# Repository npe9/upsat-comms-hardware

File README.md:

# UPSat communications hardware

Hardware for UPSat communications subsystem and for the antenna deployment mechanism. This repository includes all needed.

## Documentation

## Repository policy
UPSat hardware repositories only track source design files. All needed derivative files (e.g. stl, grb etc) for production are created per release, packaged in an archive and uploaded linked to a  [release](*link needed*).

Each major release (x.0.0) is branched out of master. Subsequent fixes (minor or not) are commited on those branches and tagged accordingly.

Master branch is most times under active development, so expect things to break. For production ready and previous releases source files check tags and branches.

## License

&copy; 2016 Manos Theodoridis - APEL - University of Patras
&copy; 2016 Libre Space Foundation & commiters

Licensed under the [CERN OHLv1.2](LICENSE).

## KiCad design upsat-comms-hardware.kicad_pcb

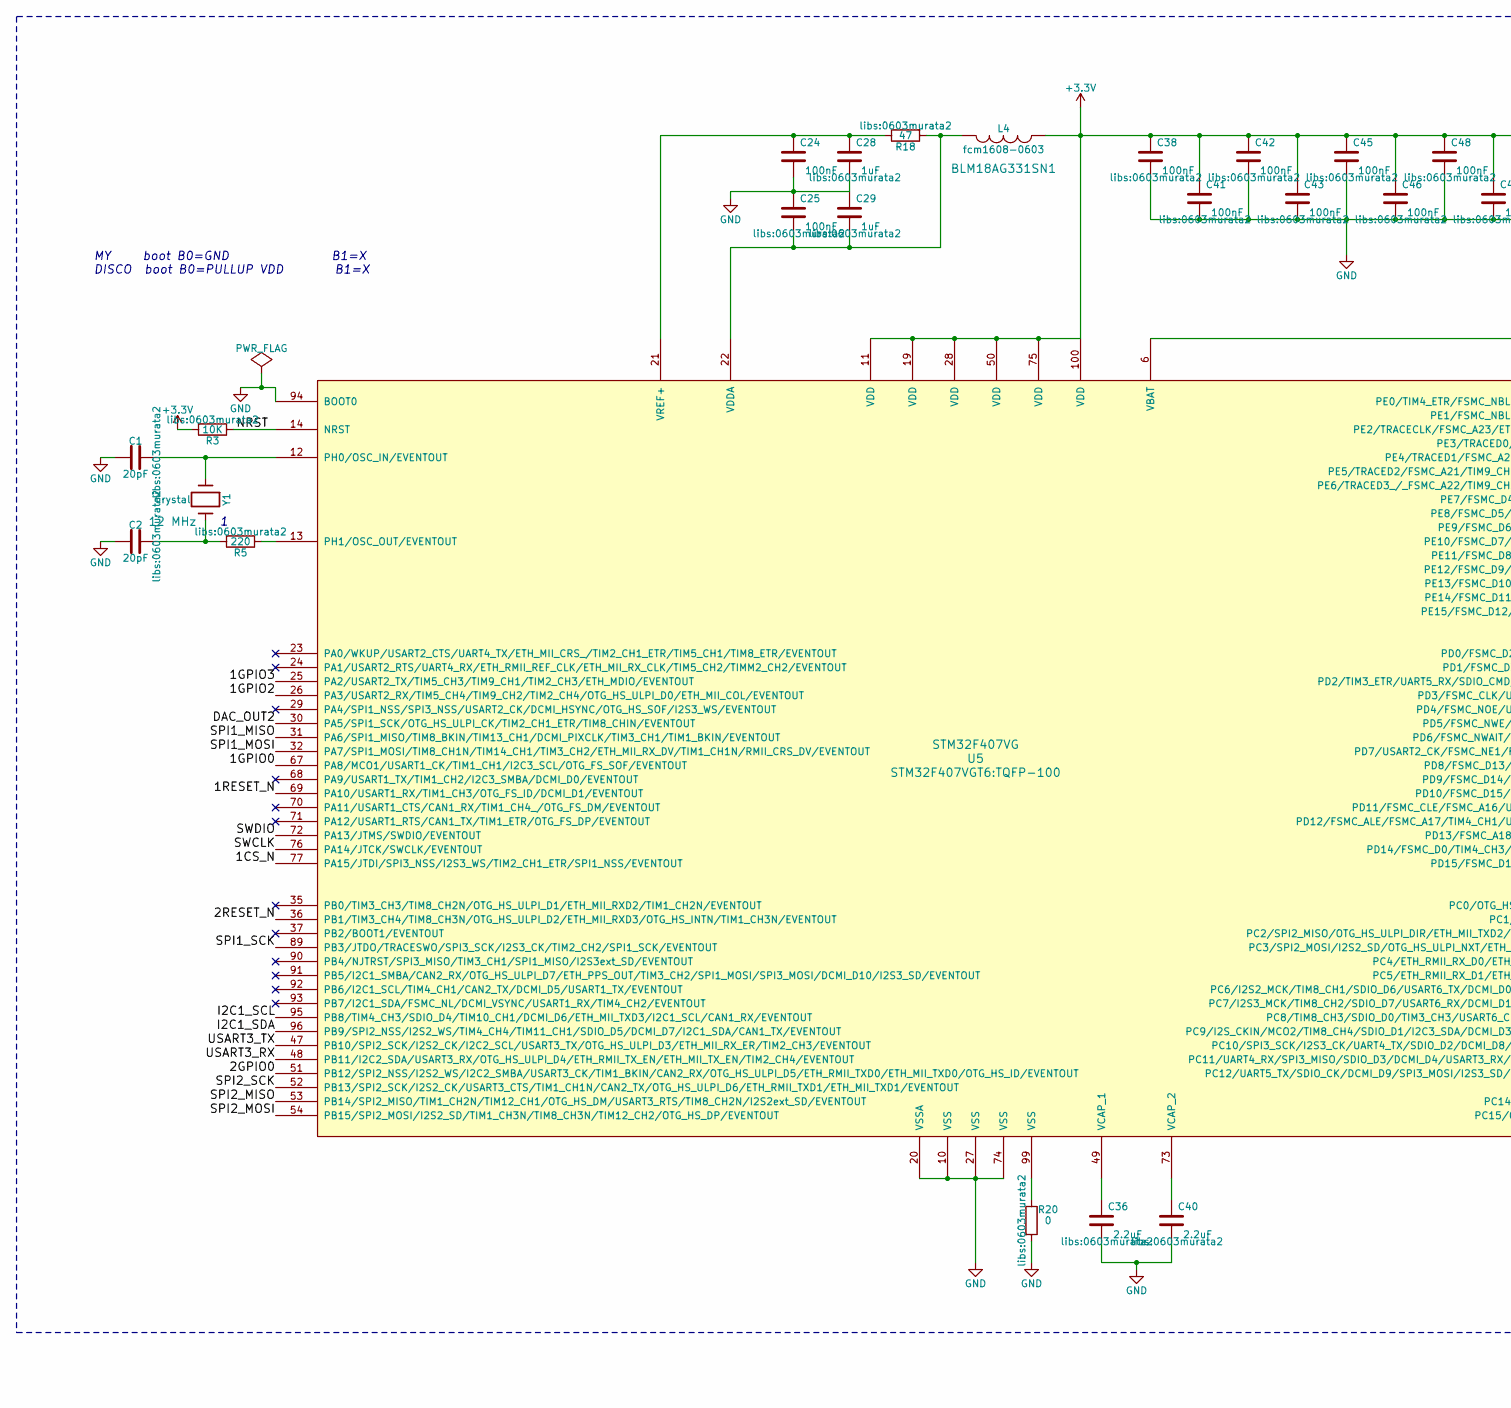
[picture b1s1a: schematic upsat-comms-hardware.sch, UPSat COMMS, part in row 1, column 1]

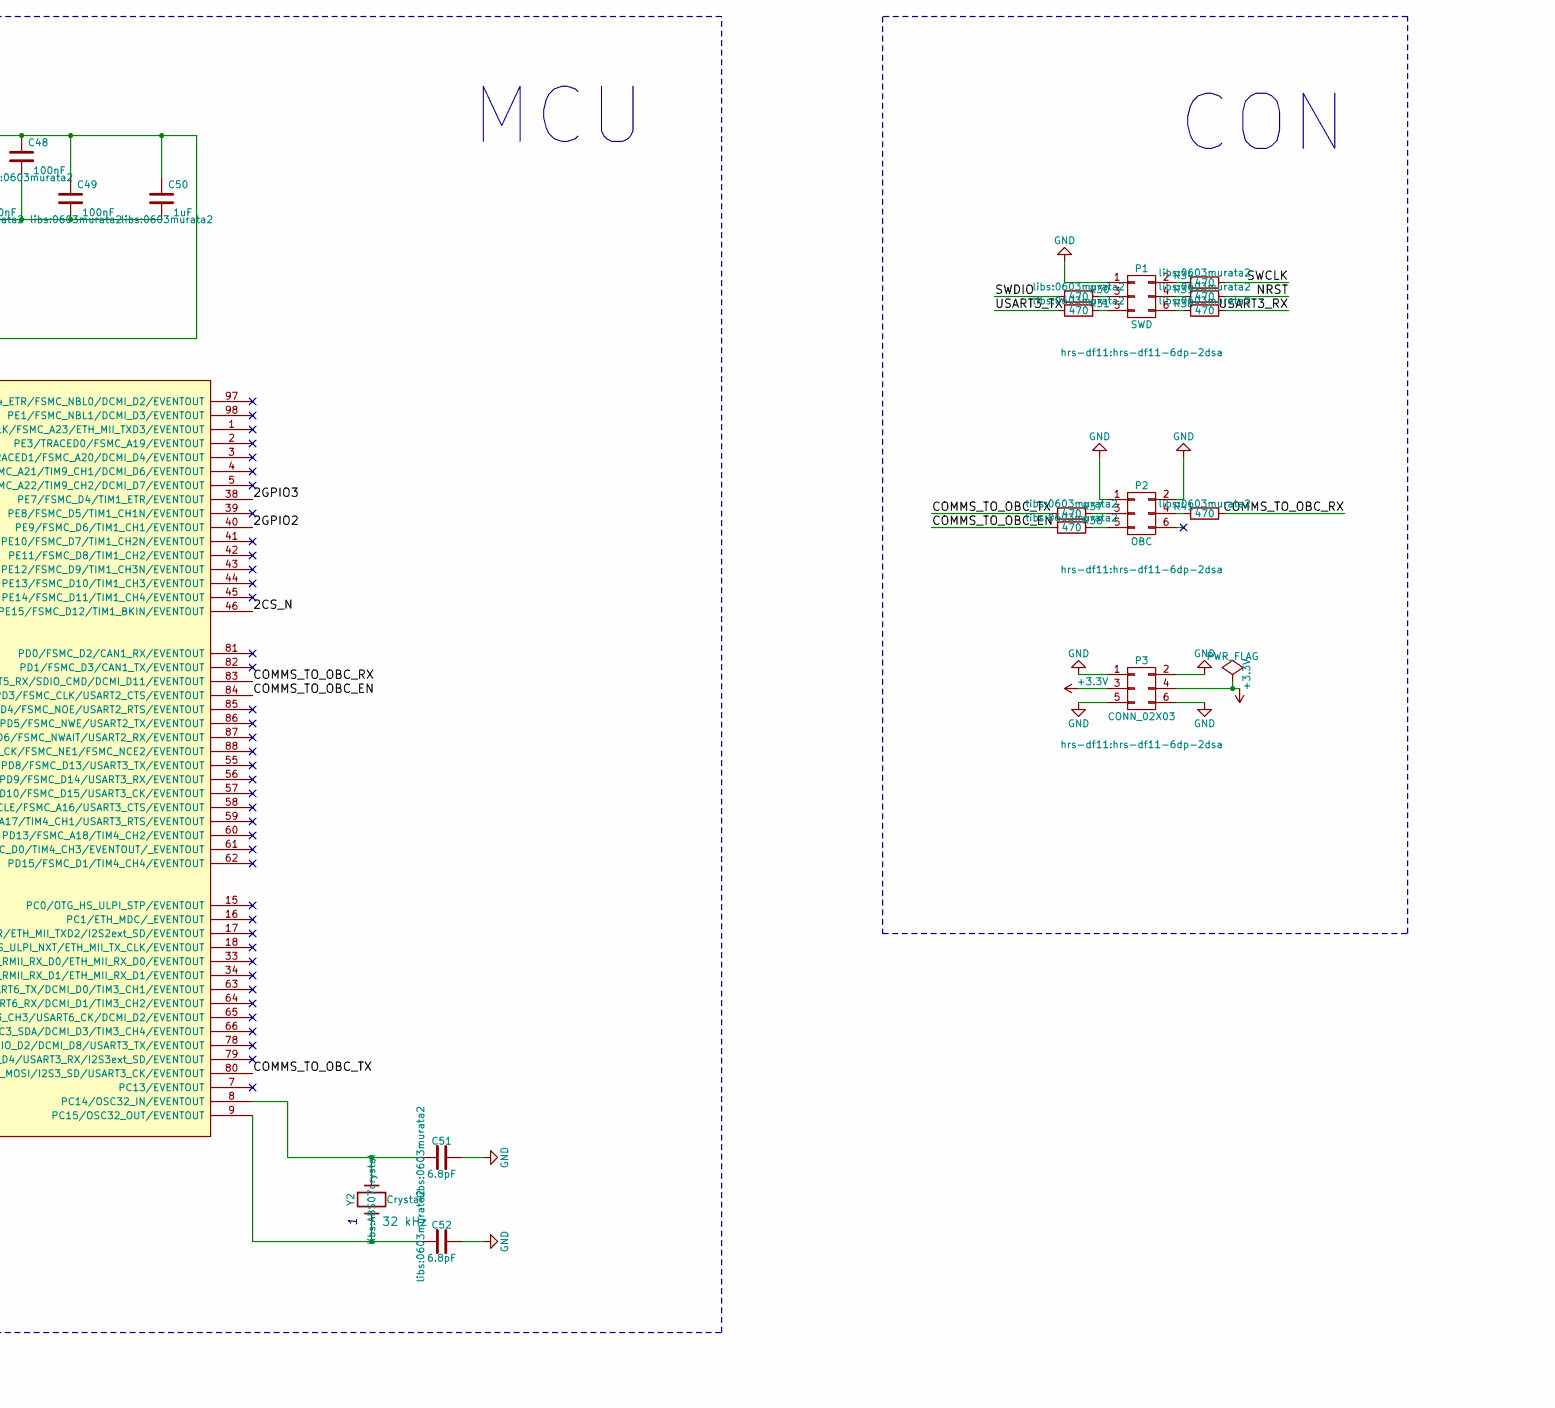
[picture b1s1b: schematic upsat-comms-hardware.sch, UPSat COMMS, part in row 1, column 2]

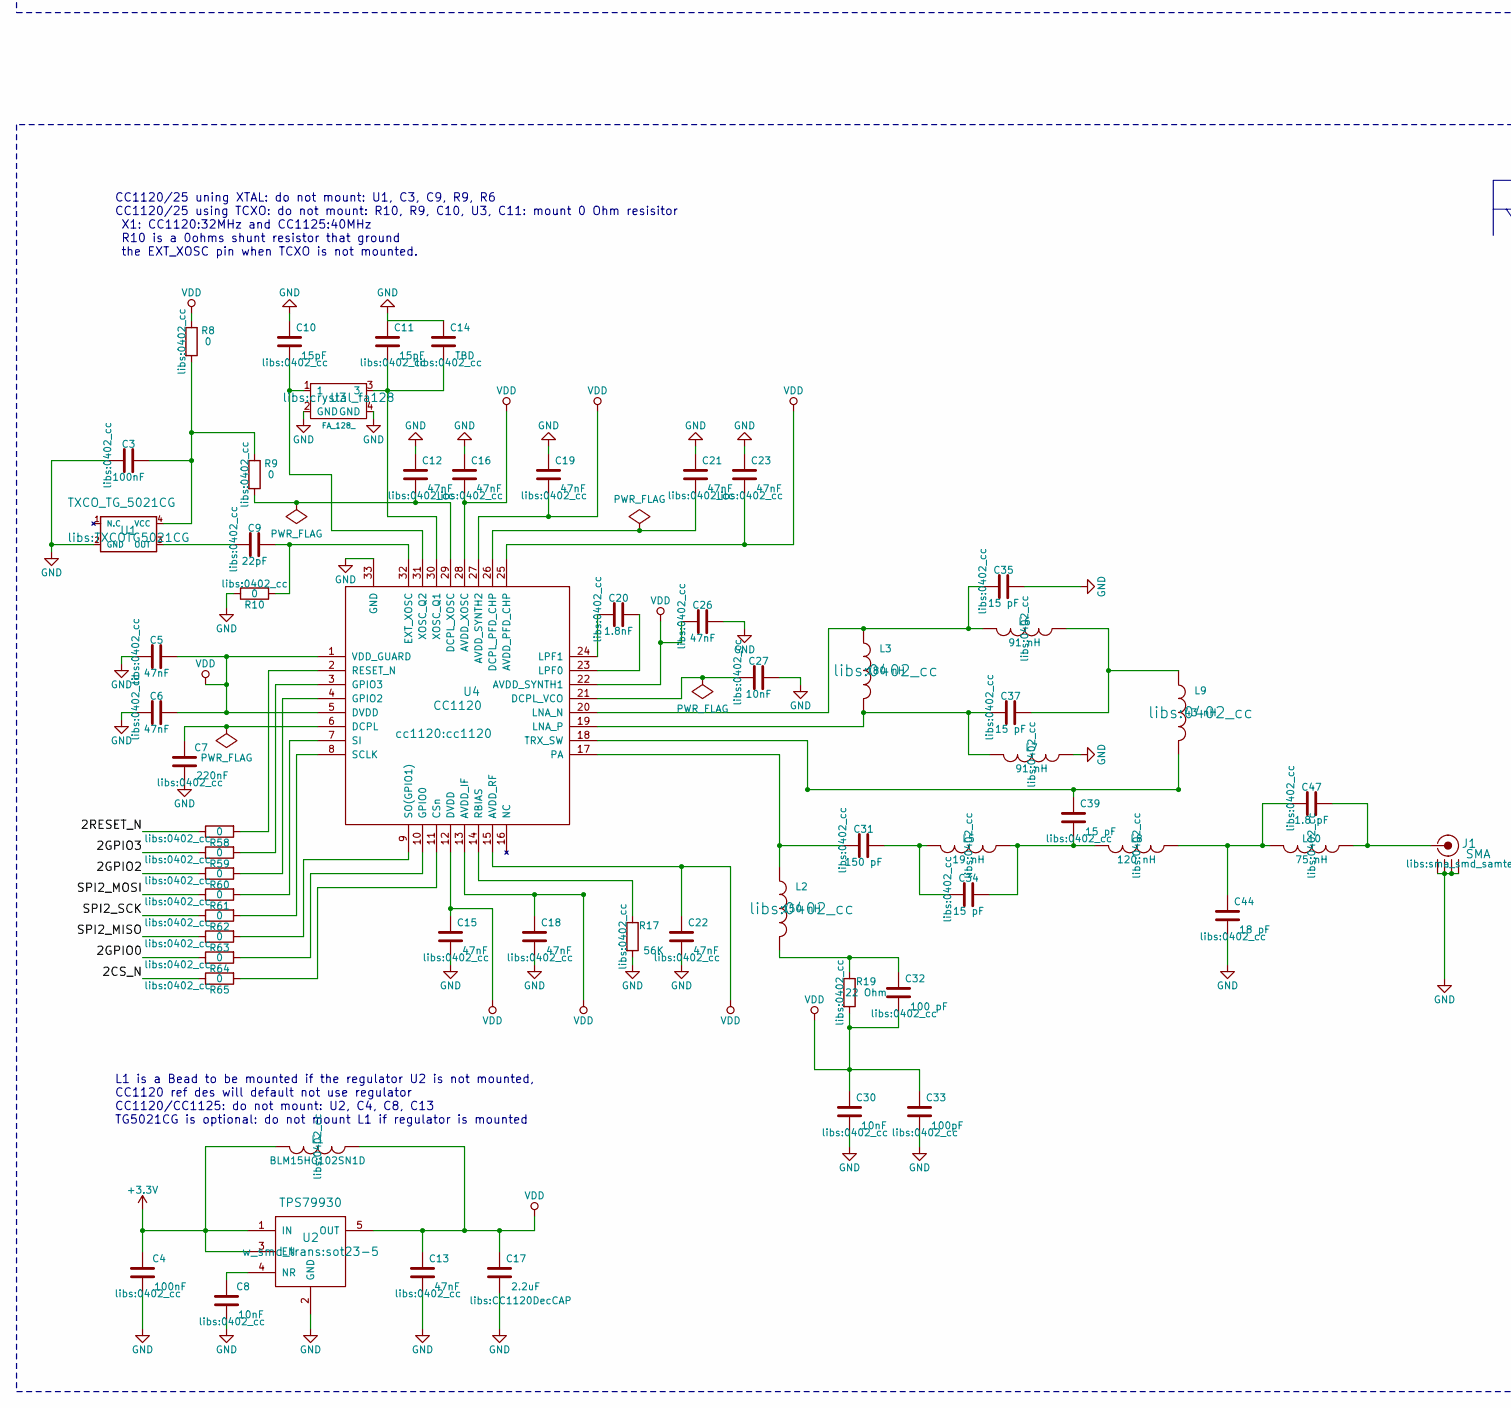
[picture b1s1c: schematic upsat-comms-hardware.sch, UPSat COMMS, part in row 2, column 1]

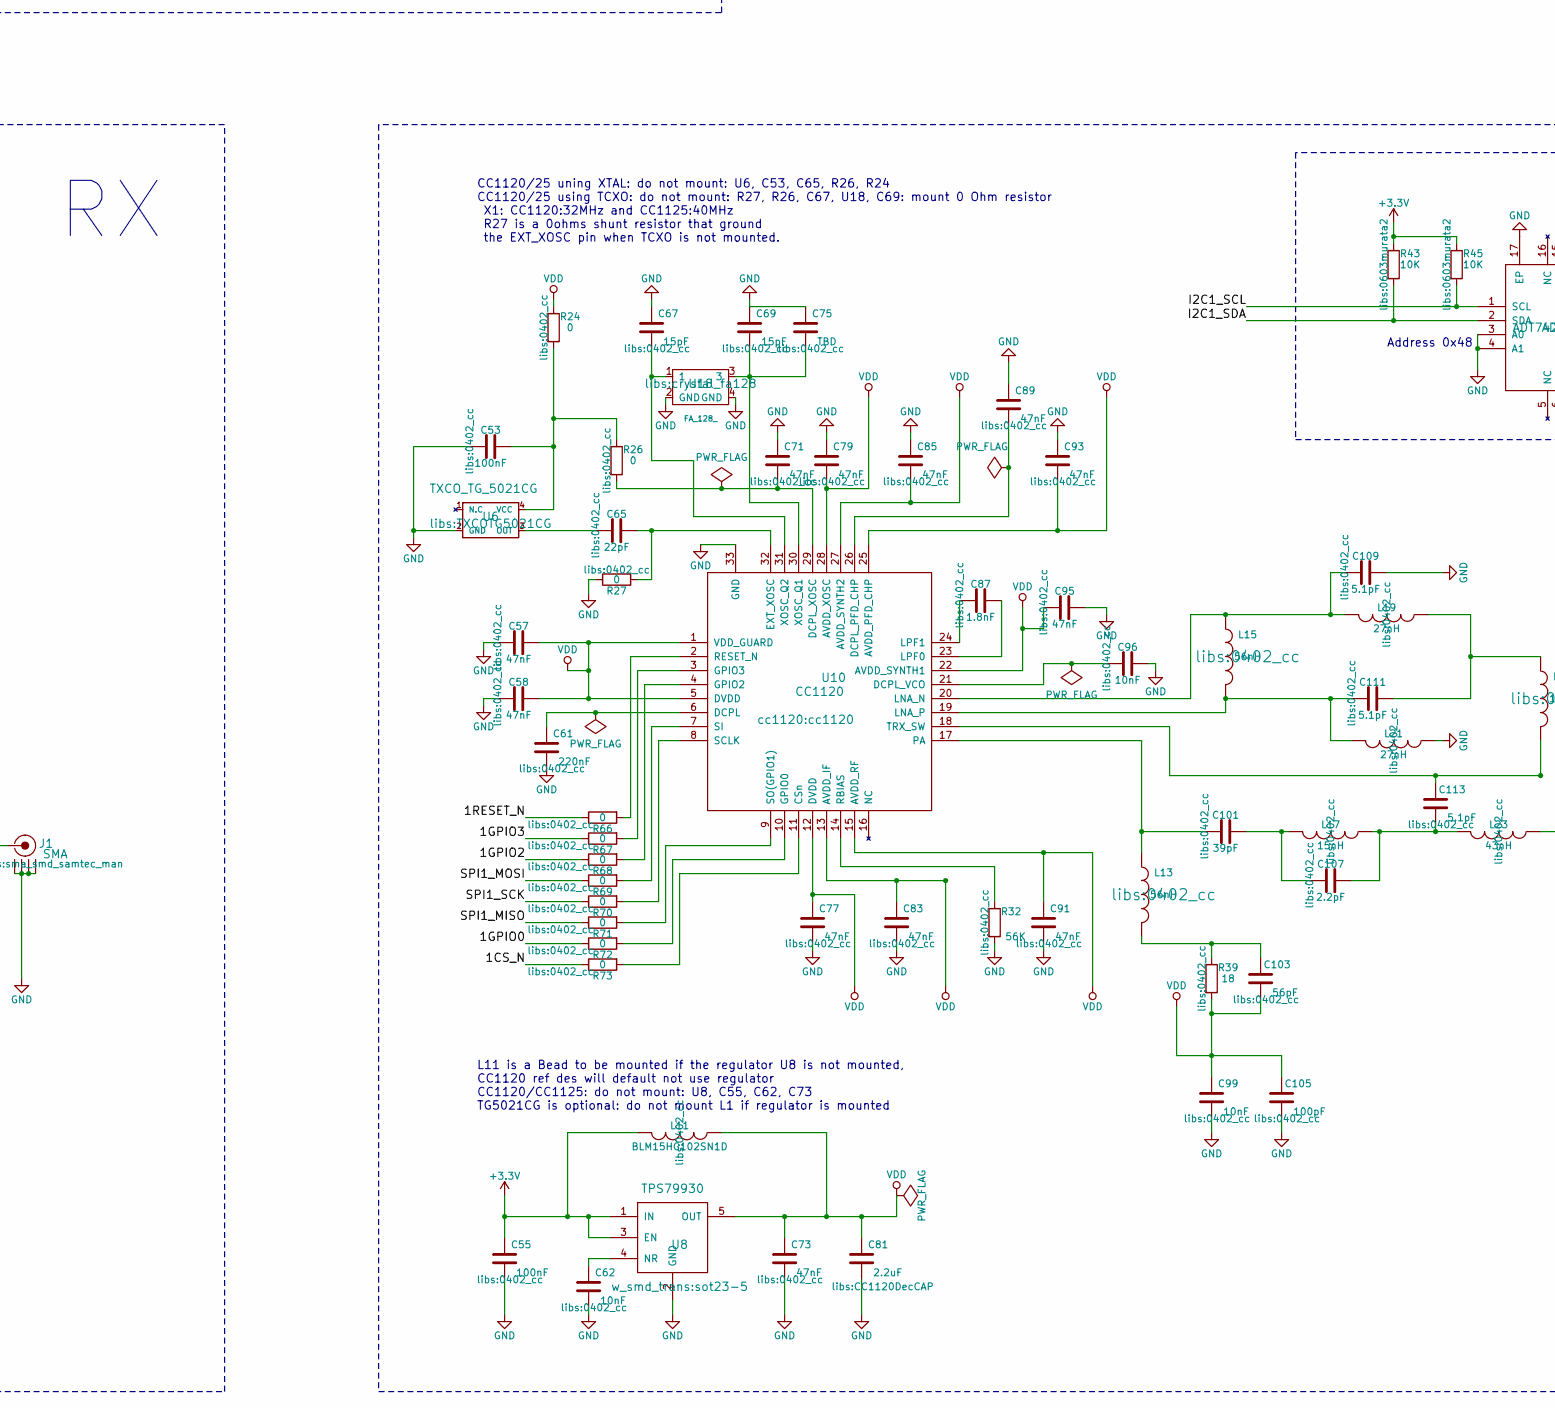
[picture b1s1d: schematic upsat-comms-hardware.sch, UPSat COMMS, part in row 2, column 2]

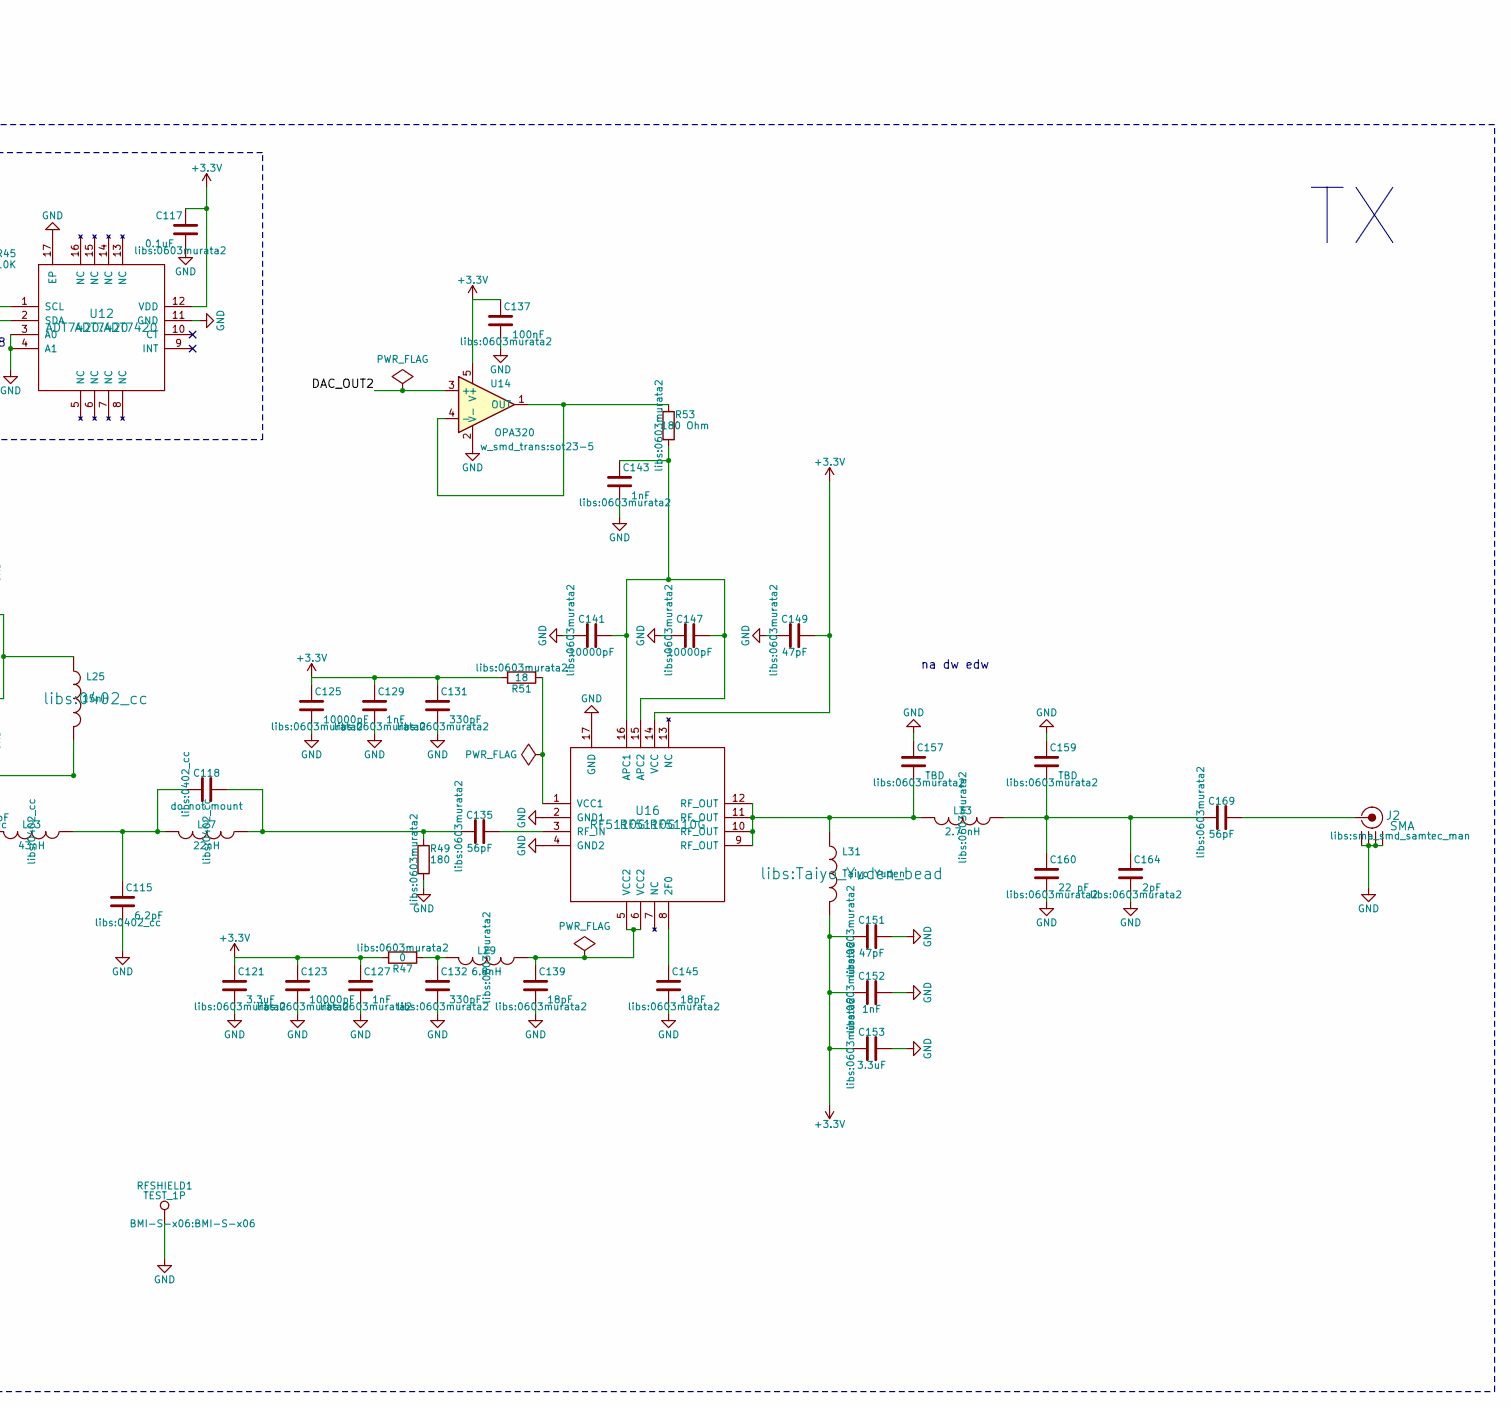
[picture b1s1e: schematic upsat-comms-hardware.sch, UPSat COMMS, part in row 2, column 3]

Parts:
C1, C2: 20pF; 0603murata2
C3, C4, C53, C55: 100nF; 0402_cc
C5, C6, C12, C13, C15, C16, C18, C19, C21, C22, C23, C26, C57, C58, C71, C73, C77, C79, C83, C85, C89, C91, C93, C95: 47nF; 0402_cc
C7, C61: 220nF; 0402_cc
C8, C27, C30, C62, C96, C99: 10nF; 0402_cc
C9, C65: 22pF; 0402_cc
C10, C11, C67, C69: 15pF; 0402_cc
C14, C75: TBD; 0402_cc
C17, C81: 2.2uF; CC1120DecCAP
C20, C87: 1.8nF; 0402_cc
C24, C25, C38, C41, C42, C43, C45, C46, C48, C49, C137: 100nF; 0603murata2
C28, C29, C50: 1uF; 0603murata2
C31: 150 pF; 0402_cc
C32: 100 pF; 0402_cc
C33, C105: 100pF; 0402_cc
C34, C35, C37, C39: 15 pF; 0402_cc
C36, C40: 2.2uF; 0603murata2
C44: 18 pF; 0402_cc
C47: 1.8 pF; 0402_cc
C51, C52: 6.8pF; 0603murata2
C101: 39pF; 0402_cc
C103: 56pF; 0402_cc
C107: 2.2pF; 0402_cc
C109, C111, C113: 5.1pF; 0402_cc
C115: 6.2pF; 0402_cc
C117: 0.1uF; 0603murata2
C118: do not mount; 0402_cc
C121, C153: 3.3uF; 0603murata2
C123, C125, C141, C147: 10000pF; 0603murata2
C127, C129, C143, C152: 1nF; 0603murata2
C131, C132: 330pF; 0603murata2
C135, C169: 56pF; 0603murata2
C139, C145: 18pF; 0603murata2
C149, C151: 47pF; 0603murata2
C157, C159: TBD; 0603murata2
C160: 22 pF; 0603murata2
C164: 2pF; 0603murata2
J1, J2: SMA; sma_smd_samtec_man
L1, L11: BLM15HG102SN1D; 0402_cc
L2: 150 nH; 0402_cc
L3: 180 nH; 0402_cc
L4: fcm1608-0603; 0603murata2
L5: 19 nH; 0402_cc
L6, L7: 91 nH; 0402_cc
L8: 120 nH; 0402_cc
L9: 43 nH; 0402_cc
L10: 75 nH; 0402_cc
L13, L15: 56nH; 0402_cc
L17, L25: 15nH; 0402_cc
L19, L21: 27nH; 0402_cc
L23: 43nH; 0402_cc
L27: 22nH; 0402_cc
L29: 6.8nH; 0603murata2
L31: Taiyo Yuden; Taiyo_Yuden_bead
L33: 2.7 nH; 0603murata2
P1: SWD; hrs-df11-6dp-2dsa
P2: OBC; hrs-df11-6dp-2dsa
P3: CONN_02X03; hrs-df11-6dp-2dsa
R3, R43, R45: 10K; 0603murata2
R5: 220; 0603murata2
R8, R9, R10, R24, R26, R27, R58, R59, R60, R61, R62, R63, R64, R65, R66, R67, R68, R69, R70, R71, R72, R73: 0; 0402_cc
R17, R32: 56K; 0402_cc
R18: 47; 0603murata2
R19: 22 Ohm; 0402_cc
R20, R47: 0; 0603murata2
R30, R31, R34, R35, R36, R37, R38, R41: 470; 0603murata2
R39: 18; 0402_cc
R49: 180; 0603murata2
R51: 18; 0603murata2
R53: 180 Ohm; 0603murata2
RFSHIELD1: TEST_1P; BMI-S-x06
U1, U6: TXCO_TG_5021CG; TXCOTG5021CG
U2, U8: TPS79930; sot23-5
U3, U18: FA_128_; crystal_fa128
U4, U10: CC1120; cc1120
U5: STM32F407VG; TQFP-100
U12: ADT7420
U14: OPA320; sot23-5
U16: RF5110G
Y1: Crystal; ABM3crystal
Y2: Crystal; ABS07crystal

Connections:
+3V3: C4.1, C38.1, C41.1, C42.1, C43.1, C45.1, C46.1, C48.1, C49.1, C50.1, C55.1, C117.1, C121.1, C123.1, C125.1, C127.1, C129.1, C131.1, C137.1, C149.1, C151.2, C152.2, C153.2, L1.2, L4.2, L11.2, L31.2, P3.3, P3.4, R3.2, R43.1, R45.1, R47.1, R51.1, U2.1 (IN), U2.3 (EN), U5.6 (VBAT), U5.11 (VDD), U5.19 (VDD), U5.28 (VDD), U5.50 (VDD), U5.75 (VDD), U5.100 (VDD), U8.1 (IN), U8.3 (EN), U12.12 (VDD), U14.5 (V+), U16.14 (VCC); also elsewhere on the board
/1CS_N: R73.1, U5.77 (PA15/JTDI/SPI3_NSS/I2S3_WS/TIM2_CH1_ETR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)
/1GPIO0: R72.1, U5.67 (PA8/MCO1/USART1_CK/TIM1_CH1/I2C3_SCL/OT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)
/1GPIO2: R68.1, U5.26 (PA3/USART2_RX/TIM5_CH4/TIM9_CH2/TIM2_CH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)
/1GPIO3: R67.1, U5.25 (PA2/USART2_TX/TIM5_CH3/TIM9_CH1/TIM2_CH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)
/1RESET_N: R66.1, U5.69 (PA10/USART1_RX/TIM1_CH3/OTG_FS_ID/DCMI_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)
/2CS_N: R65.1, U5.46 (PE15/FSMC_D12/TIM1_BKIN/EVENTOUT)
/2GPIO0: R64.1, U5.51 (PB12/SPI2_NSS/I2S2_WS/I2C2_SMBA/USART3_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)
/2GPIO2: R60.1, U5.40 (PE9/FSMC_D6/TIM1_CH1/EVENTOUT)
/2GPIO3: R59.1, U5.38 (PE7/FSMC_D4/TIM1_ETR/EVENTOUT)
/2RESET_N: R58.1, U5.36 (PB1/TIM3_CH4/TIM8_CH3N/OTG_HS_ULPI_D2/E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)
/COMMS_TO_OBC_EN: R38.2, U5.84 (PD3/FSMC_CLK/USART2_CTS/EVENTOUT)
/COMMS_TO_OBC_RX: R41.1, U5.83 (PD2/TIM3_ETR/UART5_RX/SDIO_CMD/DCMI_D11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)
/COMMS_TO_OBC_TX: R37.2, U5.80 (PC12/UART5_TX/SDIO_CK/DCMI_D9/SPI3_MOSI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)
/DAC_OUT2: U5.30 (PA5/SPI1_SCK/OTG_HS_ULPI_CK/TIM2_CH1_ET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), U14.3 (+)
/I2C1_SCL: R45.2, U5.95 (PB8/TIM4_CH3/SDIO_D4/TIM10_CH1/DCMI_D6/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), U12.1 (SCL)
/I2C1_SDA: R43.2, U5.96 (PB9/SPI2_NSS/I2S2_WS/TIM4_CH4/TIM11_CH1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), U12.2 (SDA)
/NRST: R3.1, R35.1, U5.14 (NRST)
/SPI1_MISO: R71.1, U5.31 (PA6/SPI1_MISO/TIM8_BKIN/TIM13_CH1/DCMI_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)
/SPI1_MOSI: R69.1, U5.32 (PA7/SPI1_MOSI/TIM8_CH1N/TIM14_CH1/TIM3_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)
/SPI1_SCK: R70.1, U5.89 (PB3/JTDO/TRACESWO/SPI3_SCK/I2S3_CK/TIM2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)
/SPI2_MISO: R63.1, U5.53 (PB14/SPI2_MISO/TIM1_CH2N/TIM12_CH1/OTG_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)
/SPI2_MOSI: R61.1, U5.54 (PB15/SPI2_MOSI/I2S2_SD/TIM1_CH3N/TIM8_C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)
/SPI2_SCK: R62.1, U5.52 (PB13/SPI2_SCK/I2S2_CK/USART3_CTS/TIM1_C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)
/SWCLK: R34.1, U5.76 (PA14/JTCK/SWCLK/EVENTOUT)
/SWDIO: R30.2, U5.72 (PA13/JTMS/SWDIO/EVENTOUT)
/USART3_RX: R36.1, U5.48 (PB11/I2C2_SDA/USART3_RX/OTG_HS_ULPI_D4/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)
/USART3_TX: R31.2, U5.47 (PB10/SPI2_SCK/I2S2_CK/I2C2_SCL/USART3_T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)
GND: C1.1, C2.1, C3.2, C4.2, C5.2, C6.2, C7.2, C8.2, C10.1, C11.1, C12.1, C13.2, C14.1, C15.2, C16.1, C17.2, C18.2, C19.1, C21.1, C22.2, C23.1, C24.2, C25.1, C26.1, C27.1, C28.2, C29.1, C30.2, C33.2, C35.1, C36.2, C38.2, C40.2, C41.2, C42.2, C43.2, C44.2, C45.2, C46.2, C48.2, C49.2, C50.2, C51.1, C52.1, C53.2, C55.2, C57.2, C58.2, C61.2, C62.2, C67.1, C69.1, C71.1, C73.2, C75.1, C77.2, C79.1, C81.2, C83.2, C85.1, C89.1, C91.2, C93.1, C95.1, C96.1, C99.2, C105.2, C109.1, C115.2, C117.2, C121.2, C123.2, C125.2, C127.2, C129.2, C131.2, C132.2, C137.2, C139.2, C141.2, C143.2, C145.2, C147.2, C149.2, C151.1, C152.1, C153.1, C157.1, C159.1, C160.2, C164.2, J1.2 (GND1), J1.3 (GND2), J1.4 (GND3), J1.5 (GND4), J2.2 (GND1), J2.3 (GND2), J2.4 (GND3), J2.5 (GND4), L7.1, L21.1, P1.1, P2.1, P2.2, P3.1, P3.2, P3.5, P3.6, R10.1, R17.2, R20.2, R27.1, R32.2, R49.2, RFSHIELD1.1, U1.2 (GND), U2.2 (GND), U3.2 (GND), U3.4 (GND), U4.33 (GND), U5.10 (VSS), U5.20 (VSSA), U5.27 (VSS), U5.74 (VSS), U5.94 (BOOT0), U6.2 (GND), U8.2 (GND), U10.33 (GND), U12.3 (A0), U12.4 (A1), U12.11 (GND), U12.17 (EP), U14.2 (V-), U16.2 (GND1), U16.4 (GND2), U16.17 (GND), U18.2 (GND), U18.4 (GND); also elsewhere on the board
unnamed: C1.2, U5.12 (PH0/OSC_IN/EVENTOUT), Y1.1
unnamed: C2.2, R5.2, Y1.2
unnamed: C3.1, R8.2, R9.1, U1.4 (VCC)
unnamed: C7.1, U4.6 (DCPL)
unnamed: C8.1, U2.4 (NR)
unnamed: C9.1, R10.2, U4.32 (EXT_XOSC)
unnamed: C9.2, U1.3 (OUT)
unnamed: C10.2, U3.1, U4.31 (XOSC_Q2)
unnamed: C11.2, C14.2, U3.3, U4.30 (XOSC_Q1)
unnamed: C12.2, R9.2, U4.29 (DCPL_XOSC)
unnamed: C20.1, U4.23 (LPF0)
unnamed: C20.2, U4.24 (LPF1)
unnamed: C21.2, U4.26 (DCPL_PFD_CHP)
unnamed: C24.1, C28.1, R18.1, U5.21 (VREF+)
unnamed: C25.2, C29.2, L4.1, R18.2, U5.22 (VDDA)
unnamed: C27.2, U4.21 (DCPL_VCO)
unnamed: C31.1, C34.2, L5.2
unnamed: C31.2, L2.1, U4.17 (PA)
unnamed: C32.1, L2.2, R19.1
unnamed: C34.1, C39.2, L5.1, L8.2
unnamed: C35.2, L3.1, L6.2, U4.20 (LNA_N)
unnamed: C36.1, U5.49 (VCAP_1)
unnamed: C37.1, L6.1, L9.1
unnamed: C37.2, L3.2, L7.2, U4.19 (LNA_P)
unnamed: C39.1, L9.2, U4.18 (TRX_SW)
unnamed: C40.1, U5.73 (VCAP_2)
unnamed: C44.1, C47.2, L8.1, L10.2
unnamed 56: C47.1, J1.1 (RF), L10.1; also elsewhere on the board
unnamed: C51.2, U5.8 (PC14/OSC32_IN/EVENTOUT), Y2.1
unnamed: C52.2, U5.9 (PC15/OSC32_OUT/EVENTOUT), Y2.2
unnamed: C53.1, R24.2, R26.1, U6.4 (VCC)
unnamed: C61.1, U10.6 (DCPL)
unnamed: C62.1, U8.4 (NR)
unnamed: C65.1, R27.2, U10.32 (EXT_XOSC)
unnamed: C65.2, U6.3 (OUT)
unnamed: C67.2, U10.31 (XOSC_Q2), U18.1
unnamed: C69.2, C75.2, U10.30 (XOSC_Q1), U18.3
unnamed: C71.2, R26.2, U10.29 (DCPL_XOSC)
unnamed: C87.1, U10.23 (LPF0)
unnamed: C87.2, U10.24 (LPF1)
unnamed: C89.2, U10.26 (DCPL_PFD_CHP)
unnamed: C96.2, U10.21 (DCPL_VCO)
unnamed: C101.1, C107.2, L17.2
unnamed: C101.2, L13.1, U10.17 (PA)
unnamed: C103.1, L13.2, R39.1
unnamed: C107.1, C113.2, L17.1, L23.2
unnamed: C109.2, L15.1, L19.2, U10.20 (LNA_N)
unnamed: C111.1, L19.1, L25.1
unnamed: C111.2, L15.2, L21.2, U10.19 (LNA_P)
unnamed: C113.1, L25.2, U10.18 (TRX_SW)
unnamed: C115.1, C118.2, L23.1, L27.2
unnamed: C118.1, C135.2, L27.1, R49.1
unnamed: C132.1, L29.2, R47.2
unnamed: C135.1, U16.3 (RF_IN)
unnamed: C139.1, L29.1, U16.5 (VCC2), U16.6 (VCC2)
unnamed: C141.1, C143.1, C147.1, R53.2, U16.15 (APC2), U16.16 (APC1)
unnamed: C145.1, U16.8 (2F0)
unnamed: C157.2, L31.1, L33.2, U16.9 (RF_OUT), U16.10 (RF_OUT), U16.11 (RF_OUT), U16.12 (RF_OUT)
unnamed: C159.2, C160.1, C164.1, C169.2, L33.1
unnamed 88: C169.1, J2.1 (RF); also elsewhere on the board
unnamed 89: P1.2, R34.2; also elsewhere on the board
unnamed 90: P1.3, R30.1; also elsewhere on the board
unnamed 91: P1.4, R35.2; also elsewhere on the board
unnamed 92: P1.5, R31.1; also elsewhere on the board
unnamed 93: P1.6, R36.2; also elsewhere on the board
unnamed 94: P2.3, R37.1; also elsewhere on the board
unnamed 95: P2.4, R41.2; also elsewhere on the board
unnamed 96: P2.5, R38.1; also elsewhere on the board
unnamed: R5.1, U5.13 (PH1/OSC_OUT/EVENTOUT)
unnamed: R17.1, U4.14 (RBIAS)
unnamed: R20.1, U5.99 (VSS)
unnamed: R32.1, U10.14 (RBIAS)
unnamed: R51.2, U16.1 (VCC1)
unnamed: R53.1, U14.1 (OUT), U14.4 (-)
unnamed: R58.2, U4.2 (RESET_N)
unnamed: R59.2, U4.3 (GPIO3)
unnamed: R60.2, U4.4 (GPIO2)
unnamed: R61.2, U4.7 (SI)
unnamed: R62.2, U4.8 (SCLK)
unnamed: R63.2, U4.9 (SO(GPIO1))
unnamed: R64.2, U4.10 (GPIO0)
unnamed: R65.2, U4.11 (CSn)
unnamed: R66.2, U10.2 (RESET_N)
unnamed: R67.2, U10.3 (GPIO3)
unnamed: R68.2, U10.4 (GPIO2)
unnamed: R69.2, U10.7 (SI)
unnamed: R70.2, U10.8 (SCLK)
unnamed: R71.2, U10.9 (SO(GPIO1))
unnamed: R72.2, U10.10 (GPIO0)
unnamed: R73.2, U10.11 (CSn)
VDD: C5.1, C6.1, C13.1, C15.1, C16.2, C17.1, C18.1, C19.2, C22.1, C23.2, C26.2, C30.1, C32.2, C33.1, C57.1, C58.1, C73.1, C77.1, C79.2, C81.1, C83.1, C85.2, C91.1, C93.2, C95.2, C99.1, C103.2, C105.1, L1.1, L11.1, R8.1, R19.2, R24.1, R39.2, U2.5 (OUT), U4.1 (VDD_GUARD), U4.5 (DVDD), U4.12 (DVDD), U4.13 (AVDD_IF), U4.15 (AVDD_RF), U4.22 (AVDD_SYNTH1), U4.25 (AVDD_PFD_CHP), U4.27 (AVDD_SYNTH2), U4.28 (AVDD_XOSC), U8.5 (OUT), U10.1 (VDD_GUARD), U10.5 (DVDD), U10.12 (DVDD), U10.13 (AVDD_IF), U10.15 (AVDD_RF), U10.22 (AVDD_SYNTH1), U10.25 (AVDD_PFD_CHP), U10.27 (AVDD_SYNTH2), U10.28 (AVDD_XOSC)

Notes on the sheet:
MY boot B0=GND B1=X DISCO boot B0=PULLUP VDD B1=X
L1 is a Bead to be mounted if the regulator U2 is not mounted, CC1120 ref des will default not use regulator CC1120/CC1125: do not mount: U2, C4, C8, C13 TG5021CG is optional: do not mount L1 if regulator is mounted
CC1120/25 uning XTAL: do not mount: U1, C3, C9, R9, R6 CC1120/25 using TCXO: do not mount: R10, R9, C10, U3, C11: mount 0 Ohm resisitor X1: CC1120:32MHz and CC1125:40MHz R10 is a 0ohms shunt resistor that ground the EXT_XOSC pin when TCXO is not mounted.
na dw edw
CC1120/25 uning XTAL: do not mount: U6, C53, C65, R26, R24 CC1120/25 using TCXO: do not mount: R27, R26, C67, U18, C69: mount 0 Ohm resistor X1: CC1120:32MHz and CC1125:40MHz R27 is a 0ohms shunt resistor that ground the EXT_XOSC pin when TCXO is not mounted.
Address 0x48
L11 is a Bead to be mounted if the regulator U8 is not mounted, CC1120 ref des will default not use regulator CC1120/CC1125: do not mount: U8, C55, C62, C73 TG5021CG is optional: do not mount L1 if regulator is mounted
MCU
CON

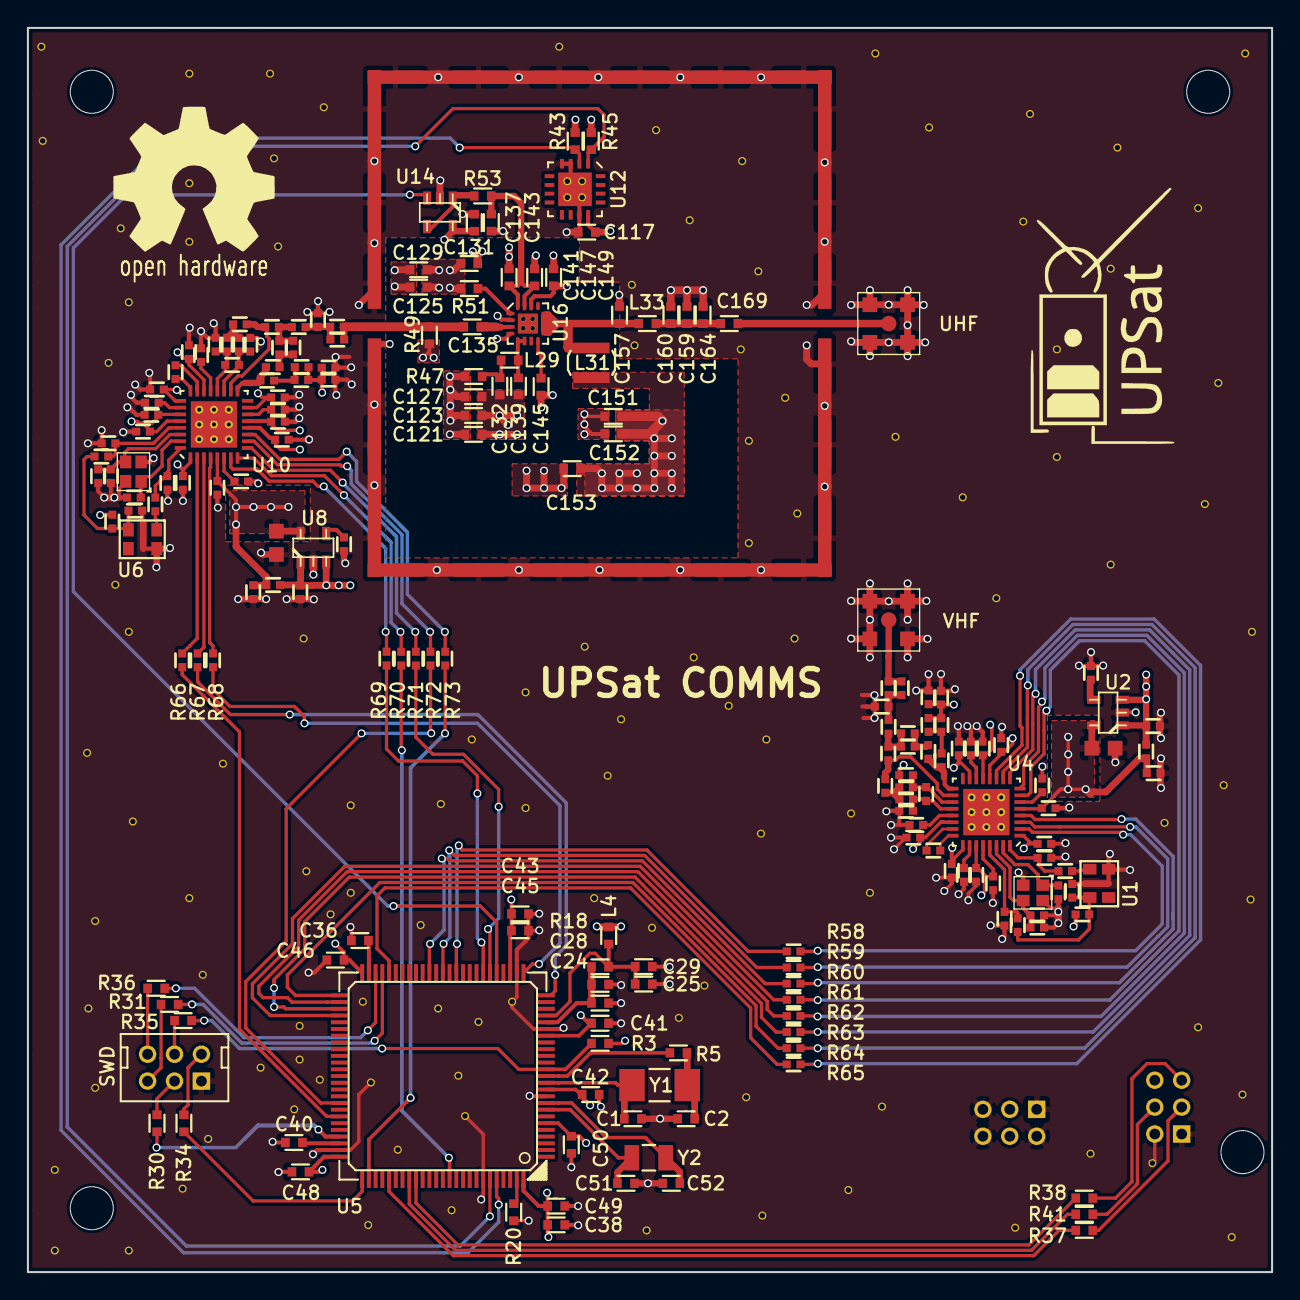
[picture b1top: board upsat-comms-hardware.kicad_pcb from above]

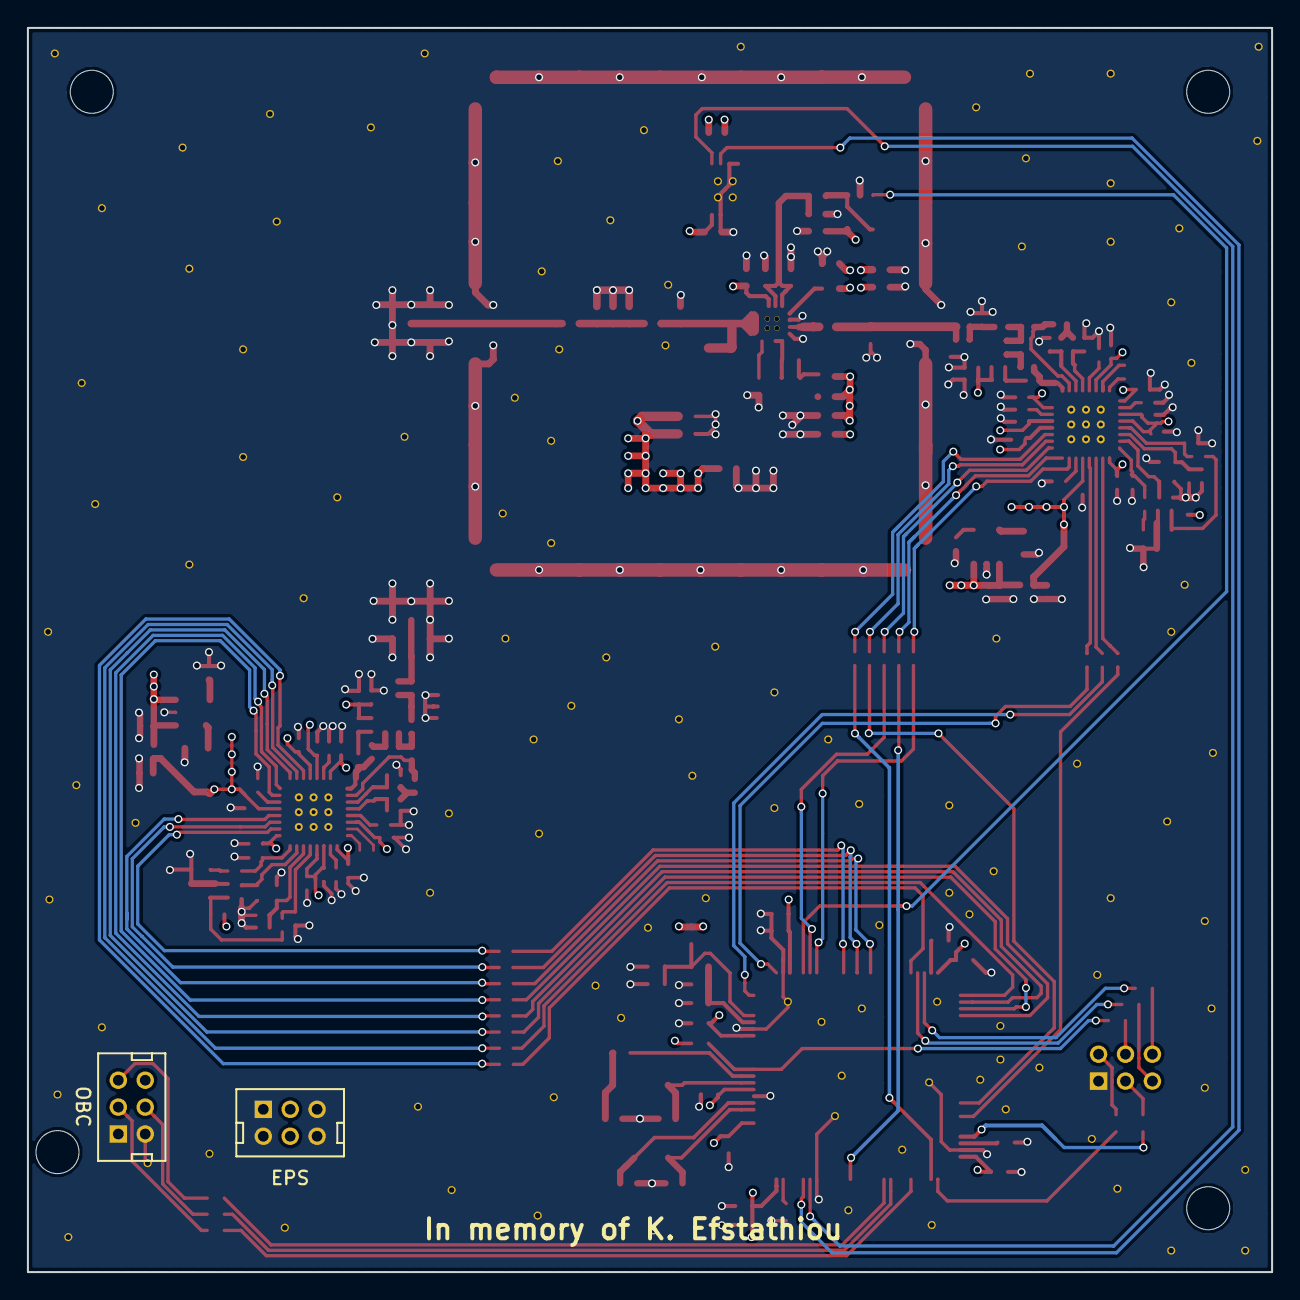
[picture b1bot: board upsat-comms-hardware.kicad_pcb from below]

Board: 4 copper layers, 92.5 x 92.5 mm, 195 parts (2 on the bottom side), 120 nets.

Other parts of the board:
EPS: CONN_02X03; hrs-df11-6dp-2dsa
OBC: OBC; hrs-df11-6dp-2dsa
SWD: SWD; hrs-df11-6dp-2dsa
UHF: SMA; mmcx_conn
VHF: SMA; mmcx_conn

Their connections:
+3V3: EPS.3, EPS.4; also elsewhere on the board
GND: EPS.1, EPS.2, EPS.5, EPS.6, OBC.1, OBC.2, SWD.1, UHF.2, UHF.3, UHF.4, UHF.5, VHF.2, VHF.3, VHF.4, VHF.5; also elsewhere on the board
unnamed 56: VHF.1; also elsewhere on the board
unnamed 88: UHF.1; also elsewhere on the board
unnamed 89: SWD.2; also elsewhere on the board
unnamed 90: SWD.3; also elsewhere on the board
unnamed 91: SWD.4; also elsewhere on the board
unnamed 92: SWD.5; also elsewhere on the board
unnamed 93: SWD.6; also elsewhere on the board
unnamed 94: OBC.3; also elsewhere on the board
unnamed 95: OBC.4; also elsewhere on the board
unnamed 96: OBC.5; also elsewhere on the board

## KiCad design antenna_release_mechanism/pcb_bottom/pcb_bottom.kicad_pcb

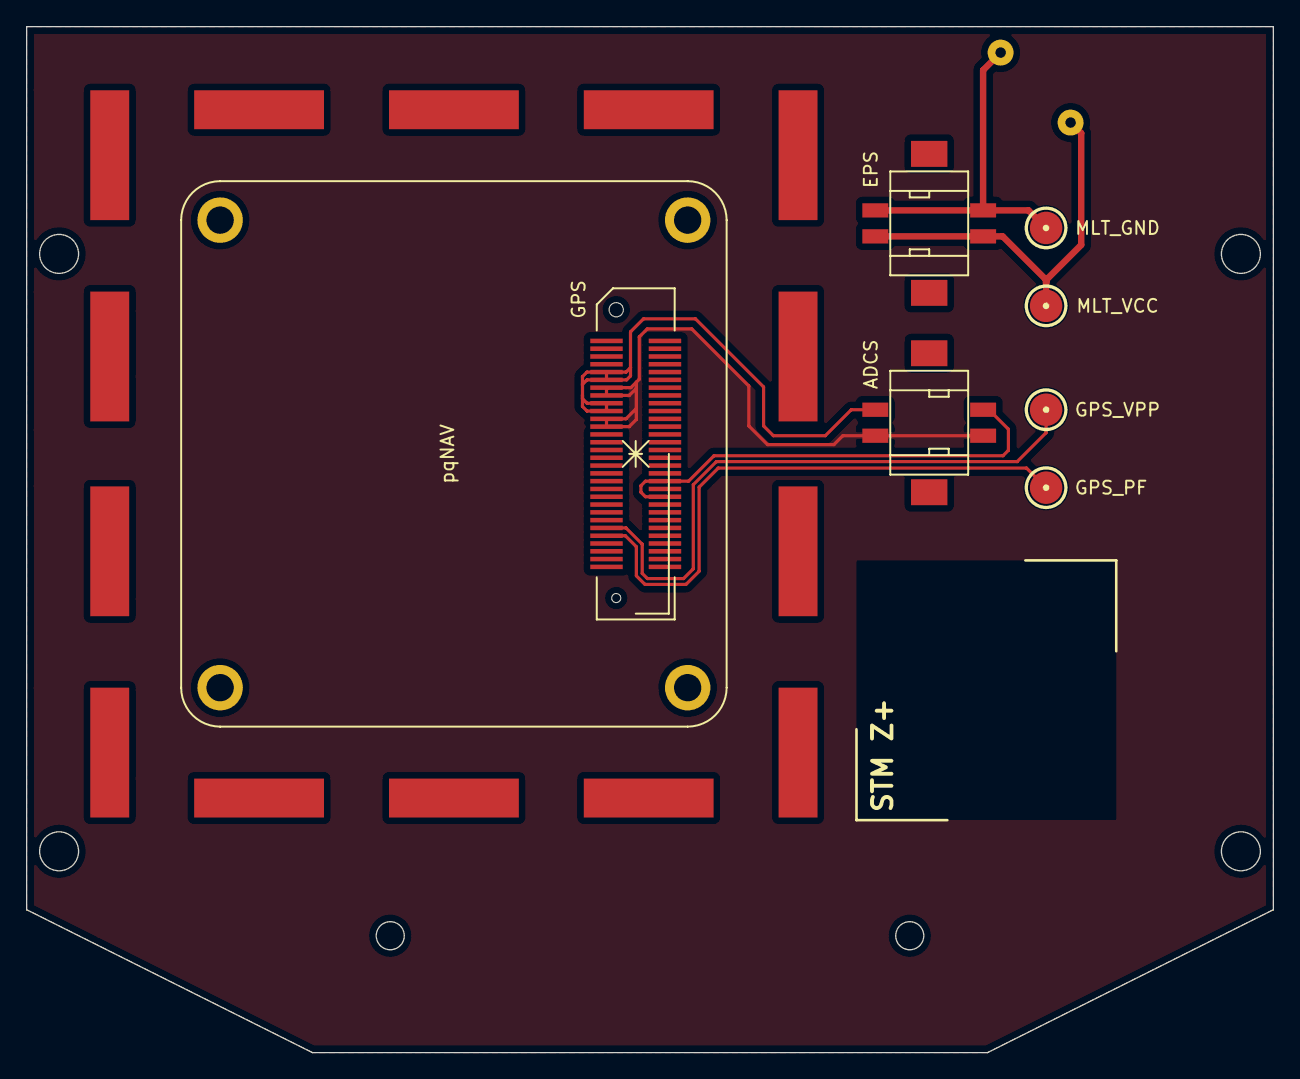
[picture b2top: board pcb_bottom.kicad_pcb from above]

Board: 2 copper layers, 96.0 x 79.0 mm, 9 parts (1 on the bottom side), 7 nets.

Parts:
ADCS: CONN_02X02; hrs-df11c-4dp-2v
EPS: CONN_02X02; hrs-df11c-4dp-2v
GPS: PQ60; hrs-fx8c-60p-sv
GPS_PF: TEST_1P; testpoint_2mm5
GPS_VPP: TEST_1P; testpoint_2mm5
MLT_GND: TEST_1P; testpoint_2mm5
MLT_VCC: TEST_1P; testpoint_2mm5
R1: R; RC03
pqNAV: GPS-pqNav

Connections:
/GPS_GND: ADCS.1, ADCS.2, GPS.7, GPS.8, GPS.11, GPS.12
/GPS_PF: GPS.26, GPS_PF.1
/GPS_TXD: ADCS.4, GPS.40, GPS.42
/GPS_VDD: ADCS.3, GPS.5, GPS.6, GPS.9, GPS.10
/GPS_VPP: GPS.25, GPS_VPP.1
/MELT_GND: EPS.1, EPS.2, MLT_GND.1, R1.2
/MELT_VCC: EPS.3, EPS.4, MLT_VCC.1, R1.1
